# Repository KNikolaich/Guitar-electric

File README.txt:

ПРЕДУСИЛИТЕЛЬ ДЛЯ ГИТАРЫ: буфер + 2-полосный темброблок, 1S Li-ion,
громкость B500K push-pull (актив/пассив), светодиод питания
=============================================================================

СОСТАВ
  kicad/            проект KiCad 7+ (схема A3, плата, файл проекта)
  schematic.pdf     принципиальная схема (детали «вне платы» — в пунктирной рамке)
  etching/          для ЛУТ / фоторезиста, масштаб 1:1
     1_ETCH_bottom_copper_print_100pct.pdf   <- ПЕЧАТАТЬ ЭТО
     2_bottom_copper_as_seen_from_copper_side.pdf  (для сверки)
     3_assembly_top_100pct.pdf               расстановка деталей
  gerbers/          Gerber + сверловка (1 слой) для заказа на фабрике
  perfboard/        макетки: 30x70 мм (24x10 отв., компактная) и 61x41 мм (24x16 отв.)
  wiring_guitar.png проводка в корпусе: звукосниматели, RV1 push-pull, джек, TP4056, LED
  BOM.csv           перечень деталей (выводная плата)
  --- SMD-вариант конечной платы 60x29 мм ---
  kicad_smd/        проект KiCad: схема (та же, футпринты SMD) + плата
  etching_smd/      1_ETCH_bottom_copper_print_100pct.pdf  <- ПЕЧАТАТЬ ЭТО
  assembly_smd/     сборочный чертёж со стороны меди + подписи площадок сверху
  gerbers_smd/      Gerber + сверловка
  BOM_SMD.csv       перечень деталей SMD

ИЗМЕНЕНИЯ ОТНОСИТЕЛЬНО ПЕРВОЙ ВЕРСИИ
  - Громкость RV1 (B500K, Musiclily M908) стоит ДО платы, сразу после переключателя
    звукоснимателей, и работает в обоих режимах. На лепестках 3–2 стоит treble bleed (150k ‖ 1n).
  - Push-pull (DPDT) RV1:
      секция A: A2 (общий) → Tip;  A3 ← OUT платы (актив);  A1 — свободен (пассив)
      секция B: B5 (общий) ← движок RV1;  B6 → IN платы (актив);  B4 → Tip (пассив)
    Какое положение ручки какое — проверить тестером; при необходимости поменять
    местами провода на крайних лепестках ОБЕИХ секций (A1<->A3 и B4<->B6).
    В пассиве и вход, и выход платы отключены от сигнала — байпас работает
    даже с полностью севшим аккумулятором.
  - Один выходной джек — СТЕРЕО-гнездо TRS, кабель обычный моно. Ring ← OUT− модуля TP4056:
    штекер замыкает Ring на Sleeve и включает питание, кабель вынут — выключено.
  - На плате больше нет площадок VOL. Выход: C9 -> R9 -> OUT, R13 100k на землю
    (без щелчков при переключении).
  - C1 = 47 пФ (меньше «съедает» верх вместе с потенциометром 500k).
  - Светодиод D1 (через R15 4.7k, ~0.4 мА) — индикатор питания. Горит, когда
    вставлен кабель и аккумулятор жив. Двухсекционный push-pull полностью занят
    сигналом, поэтому плата получает питание и в пассиве с вставленным кабелем:
    светодиод горит, плата потребляет ~1–2.5 мА, но в звуке не участвует.
    Чтобы светодиод и питание отключались и в пассиве, нужен 4PDT push-pull
    или отдельный тумблер.
  - U1: MCP6022 (DIP-8) или OPA2316IDR на переходнике SOIC->DIP. Схема одинаковая.
    Ставьте цанговую панельку: чипы можно менять без пайки (только без кабеля в джеке).

ПЛАТА
  70 x 50 мм, односторонняя, все детали выводные. Дорожки 0.8 мм, зазоры не
  меньше 0.4 мм, остальная медь залита землёй. Перемычек нет.
  Отверстия 0.8 мм под детали, 1.1 мм под провода.
  Площадки для проводов: IN/GND (J1), BAT+ (J2), OUT/GND (J3), LED+/LED− (J7),
  B1..B3 (BASS), T1..T3 (TREBLE), x2 (JP1).
  Печать для ЛУТ: 100% / «Фактический размер», НЕ зеркалить. Надпись «GTR PRE v3»
  на распечатке читается зеркально. Ширина контура 70.0 мм — проверьте линейкой.

ПЛАТА SMD 60 x 29 мм (kicad_smd/)
  Односторонняя, детали SMD паяются СО СТОРОНЫ МЕДИ. Перемычек нет.
  Резисторы и конденсаторы 1206, ОУ SOIC-8 (MCP6022-I/SN или OPA2316IDR,
  без панельки и переходника), C3/C9 — SMD-электролиты 4x5.4 мм.
  Дорожки 0.6 мм, зазоры 0.35 мм, заливка земли с зазором 0.5 мм.
  Все провода — по бокам, отверстия 1.0 мм (площадки 2.1 мм):
    левый край  (сверху вниз): LED−/GND, LED+, BAT+, IN, GND
    правый край (сверху вниз): GND, OUT, TRE1, BAS1, BAS2, TRE2, BAS3, TRE3
  Площадки BASS и TREBLE чередуются — так плату удалось развести без перемычек.
  Номер = номер лепестка потенциометра, как на wiring_guitar.png.
  Отличия по деталям: C10 и C12 — керамика 22 мкФ X5R 1206 вместо электролитов 100 мкФ.
  JP1 — резистор 0 Ом 1206 (или капля припоя), есть = x2.
  Все сигнальные конденсаторы (C1, C2, C4–C8) — только C0G/NP0, не X7R.
  Печать для ЛУТ: 100%, не зеркалить; «GTR PRE SMD» на распечатке читается зеркально.
  Ширина контура 60.0 мм. Сборка: сначала U1, потом 1206, электролиты и провода последними.
  Проверено: DRC без ошибок, все 34 детали соединены по схеме.

МАКЕТКА 30x70 мм (24x10 отв.) — для тесной полости
  Файлы: perfboard/perfboard_30x70_*.  Столбцы A..X по длинной стороне,
  строки 1..10 по короткой (сверху вниз, вид со стороны деталей).
  - Все резисторы стоят вертикально (корпус над выводом 1).
  - Плёночные C2, C4–C7 — шаг 5 мм; керамика C1, C8, C11 — шаг 2.5 мм;
    электролиты: 10 мкФ Ø5 мм, 100 мкФ Ø6.3 мм (шаг 2.5 мм).
  - Одна перемычка W1 (L6–L8, земля) изолированным проводом сверху, над R1.
  - Высота сборки ~12 мм (самые высокие — электролиты и стоящие резисторы).
  Связность проверена скриптом против схемы.

МАКЕТКА 61x41 мм (24x16 отв.)
  Файлы: perfboard/perfboard_component_side.png и т.д. Три перемычки W1–W3,
  координаты — в perfboard_coordinates.txt.

ПРОВЕРКА ПОСЛЕ ПАЙКИ
  1. Без ОУ вставьте моно-штекер в джек: на выводе 8 панельки 3.0–4.2 В, светодиод горит.
  2. С ОУ: на выводах 5, 1, 7 около половины питания (~1.85 В).
     Ток: MCP6022 ~2.5 мА, OPA2316 ~1.2 мА (вместе со светодиодом).
  3. Ручка нажата — звук идёт через темброблок (BASS/TREBLE работают).
     Ручка вытянута — темброблок не действует (пассив).

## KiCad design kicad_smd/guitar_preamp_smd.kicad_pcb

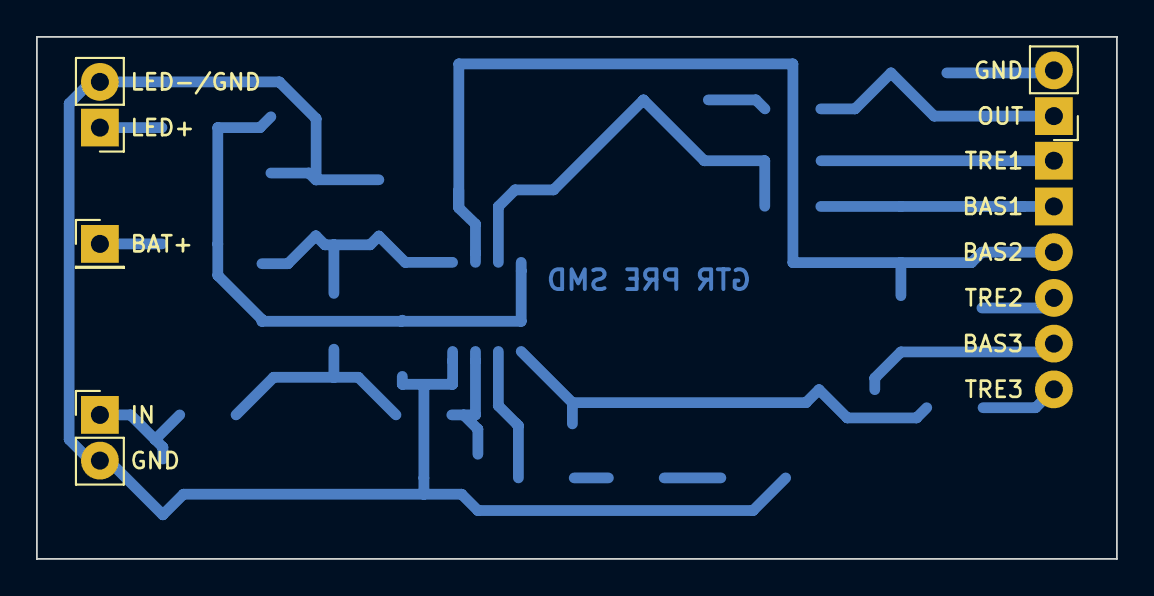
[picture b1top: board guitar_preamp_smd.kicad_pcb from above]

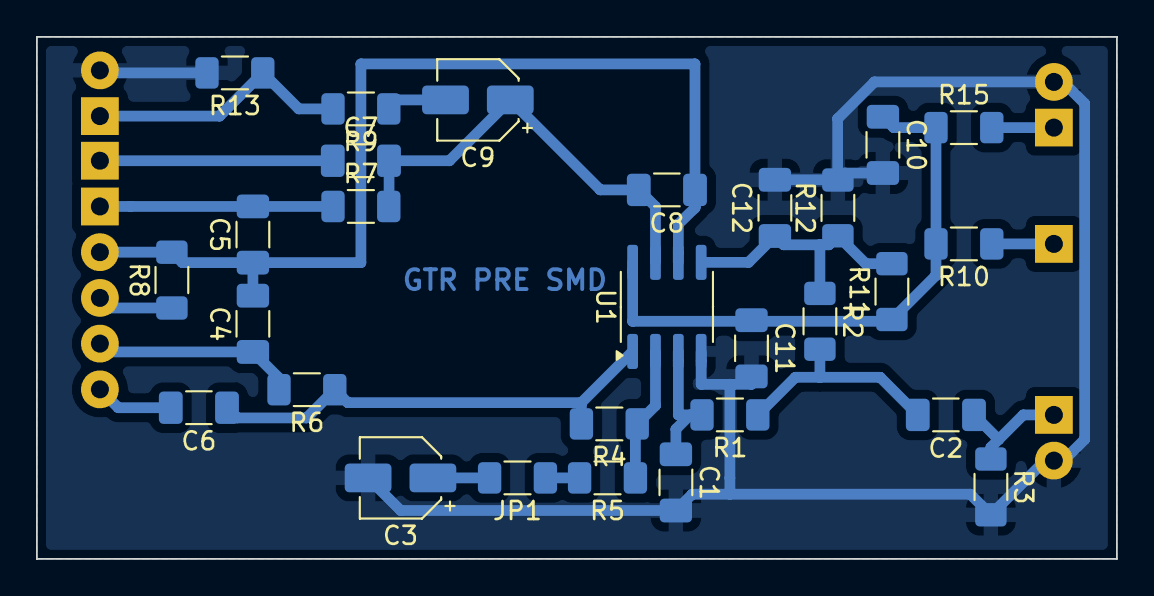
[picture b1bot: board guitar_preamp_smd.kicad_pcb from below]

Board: 2 copper layers, 60.0 x 29.0 mm, 34 parts (28 on the bottom side), 21 nets.

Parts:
C1: 47p; C_1206_3216Metric_Pad1.33x1.80mm_HandSolder
C2, C11: 100n; C_1206_3216Metric_Pad1.33x1.80mm_HandSolder
C3, C9: 10u; CP_Elec_4x5.4
C4, C5: 22n; C_1206_3216Metric_Pad1.33x1.80mm_HandSolder
C6, C7: 3.3n; C_1206_3216Metric_Pad1.33x1.80mm_HandSolder
C8: 100p; C_1206_3216Metric_Pad1.33x1.80mm_HandSolder
C10, C12: 22u; C_1206_3216Metric_Pad1.33x1.80mm_HandSolder
J1: IN (от SW1B, экранир. провод); PinHeader_1x02_P2.54mm_Vertical
J2: BAT+ (TP4056 OUT+); PinHeader_1x01_P2.54mm_Vertical
J3: OUT (к SW1A) / GND; PinHeader_1x02_P2.54mm_Vertical
J7: LED (A / K); PinHeader_1x02_P2.54mm_Vertical
JP1: GAIN x2 (0R = x2); R_1206_3216Metric_Pad1.30x1.75mm_HandSolder
R1: 1k; R_1206_3216Metric_Pad1.30x1.75mm_HandSolder
R2: 2.2M; R_1206_3216Metric_Pad1.30x1.75mm_HandSolder
R3: 10M; R_1206_3216Metric_Pad1.30x1.75mm_HandSolder
R4, R5: 10k; R_1206_3216Metric_Pad1.30x1.75mm_HandSolder
R6, R7: 22k; R_1206_3216Metric_Pad1.30x1.75mm_HandSolder
R8, R15: 4.7k; R_1206_3216Metric_Pad1.30x1.75mm_HandSolder
R9: 100; R_1206_3216Metric_Pad1.30x1.75mm_HandSolder
R10: 10; R_1206_3216Metric_Pad1.30x1.75mm_HandSolder
R11, R12, R13: 100k; R_1206_3216Metric_Pad1.30x1.75mm_HandSolder
RV2: B100k BASS; PinHeader_1x03_P2.54mm_Vertical
RV3: B100k TREBLE; PinHeader_1x03_P2.54mm_Vertical
U1: MCP6022/OPA2316; SOIC-8_3.9x4.9mm_P1.27mm

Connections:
B1: C4.1, R6.2, RV2.3
B2: C5.2, R7.1, RV2.1
BAT+: J2.1, R10.1
GND: C1.2, C3.2, C10.2, C11.2, C12.2, J1.2, J3.2, J7.2, R3.2, R12.2, R13.2, U1.4
IN: C2.1, J1.1, R3.1
INA_N: R4.1, R5.1, U1.2
INB_N: C4.2, C5.1, C8.1, R8.2, RV2.2, U1.6
INP: C1.1, R1.2, U1.3
LEDA: J7.1, R15.2
N1: C2.2, R1.1, R2.2
N2: JP1.1, R5.2
N3: C3.1, JP1.2
N4: C9.2, R9.1
OUT: J3.1, R9.2, R13.1
OUTA: C6.1, R4.2, R6.1, U1.1
OUTB: C7.2, C8.2, C9.1, R7.2, U1.7
T1: C6.2, RV3.3
T2: C7.1, RV3.1
TW: R8.1, RV3.2
VCC: C10.1, C11.1, R10.2, R11.1, R15.1, U1.8
VREF: C12.1, R2.1, R11.2, R12.1, U1.5

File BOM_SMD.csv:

Позиции;Кол-во;Номинал;Тип;Корпус / футпринт;Примечание
U1;1;MCP6022-I/SN или OPA2316IDR;ОУ;SOIC-8;паяется прямо на плату (без панельки)
C1;1;47p;Конденсатор;1206;керамика C0G/NP0
C2;1;100n;Конденсатор;1206;керамика C0G/NP0 50 В (НЕ X7R — микрофонный эффект и искажения)
C4, C5;2;22n;Конденсатор;1206;керамика C0G/NP0
C6, C7;2;3.3n;Конденсатор;1206;керамика C0G/NP0
C8;1;100p;Конденсатор;1206;керамика C0G/NP0
C11;1;100n;Конденсатор;1206;керамика X7R
C10, C12;2;22u;Конденсатор;1206;керамика X5R/X7R ≥10 В (вместо электролитов 100u)
C3, C9;2;10u;Конденсатор;SMD-электролит 4x5.4 мм;"16 В; «+» по сборочному чертежу"
R1;1;1k;Резистор;1206;
R2;1;2.2M;Резистор;1206;
R3;1;10M;Резистор;1206;
R4, R5;2;10k;Резистор;1206;
R6, R7;2;22k;Резистор;1206;
R8, R15;2;4.7k;Резистор;1206;R15 — ток светодиода ~0.4 мА
R9;1;100;Резистор;1206;
R10;1;10;Резистор;1206;
R11, R12, R13;3;100k;Резистор;1206;
JP1;1;0R;Перемычка;1206;"есть = усиление x2 (+6 дБ), нет = x1; можно каплю припоя"
J1, J2, J3, J7, RV2, RV3;—;площадки;Провода;отв. 1.0 мм, площадка 2.1 мм;провода вставляются со стороны без меди
RV2;1;B100k BASS;Потенциометр;вне платы;линейный, на корпусе
RV3;1;B100k TREBLE;Потенциометр;вне платы;линейный, на корпусе
RV1 + SW1;1;B500K push-pull (Musiclily M908);Потенциометр;вне платы;громкость + DPDT актив/пассив
R14;1;150k;Резистор;вне платы;treble bleed, на лепестках 3–2 RV1
C13;1;1n;Конденсатор;вне платы;treble bleed, плёнка/C0G, на лепестках 3–2 RV1
D1;1;LED красн. 3 мм;Светодиод;вне платы;
—;1;Модуль TP4056 с защитой (DW01), USB-C;;вне платы;OUT+ → BAT+ платы, OUT− → Ring джека
—;1;Аккумулятор 1S Li-ion/LiPo 3.7 В 300–1000 мА·ч;;вне платы;
—;1;Гнездо 6.3 мм СТЕРЕО (TRS);;вне платы;Tip ← SW1 A2, Ring ← OUT− TP4056, Sleeve ← GND
—;1;Экранированный провод 1 жила;;вне платы;SW1 B6 → IN платы
